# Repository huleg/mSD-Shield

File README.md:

# mSD-Shield
The mSD-Shield is a plug-on module with microSD socket, RTC (real time clock) with battery backup, prototyping area and optional 2.8" TFT-Display with Touch-Panel for Arduino.

## Shop
* [mSD-Shield v2](http://www.watterott.com/en/mSD-Shield-v2-Data-Logging-Shield)

## Features
* microSD socket (SPI) support SD and SDHC cards (up to 32GB)
* DS1307 RTC (I2C Real-Time-Clock) with backup battery
* Optional MI0283QT-Adapter (2.8" 320x240 Display with Touch-Panel)
* Prototyping Area

## Hardware
* 
* [Schematics + Layout](https://github.com/watterott/mSD-Shield/tree/master/hardware)
* **mSD-Shield v2.x**: For Uno, Leonardo and Mega with R3-Layout (SDA+SCL next to AREF)
* **mSD-Shield v1.x**: For Uno. On Mega/Leonardo boards only Software-SPI and no RTC without hardware modifications.
* **Mega mSD-Shield v1.x**: For Uno and Mega. Uno/Mega adjustment via jumper.

## Software
* [Arduino Library and Examples](https://github.com/watterott/Arduino-Libs)
* [Old Arduino Library and Examples](https://github.com/watterott/mSD-Shield/tree/5054db114faef1bcfd9c1d165ed713a681a0edea/src)

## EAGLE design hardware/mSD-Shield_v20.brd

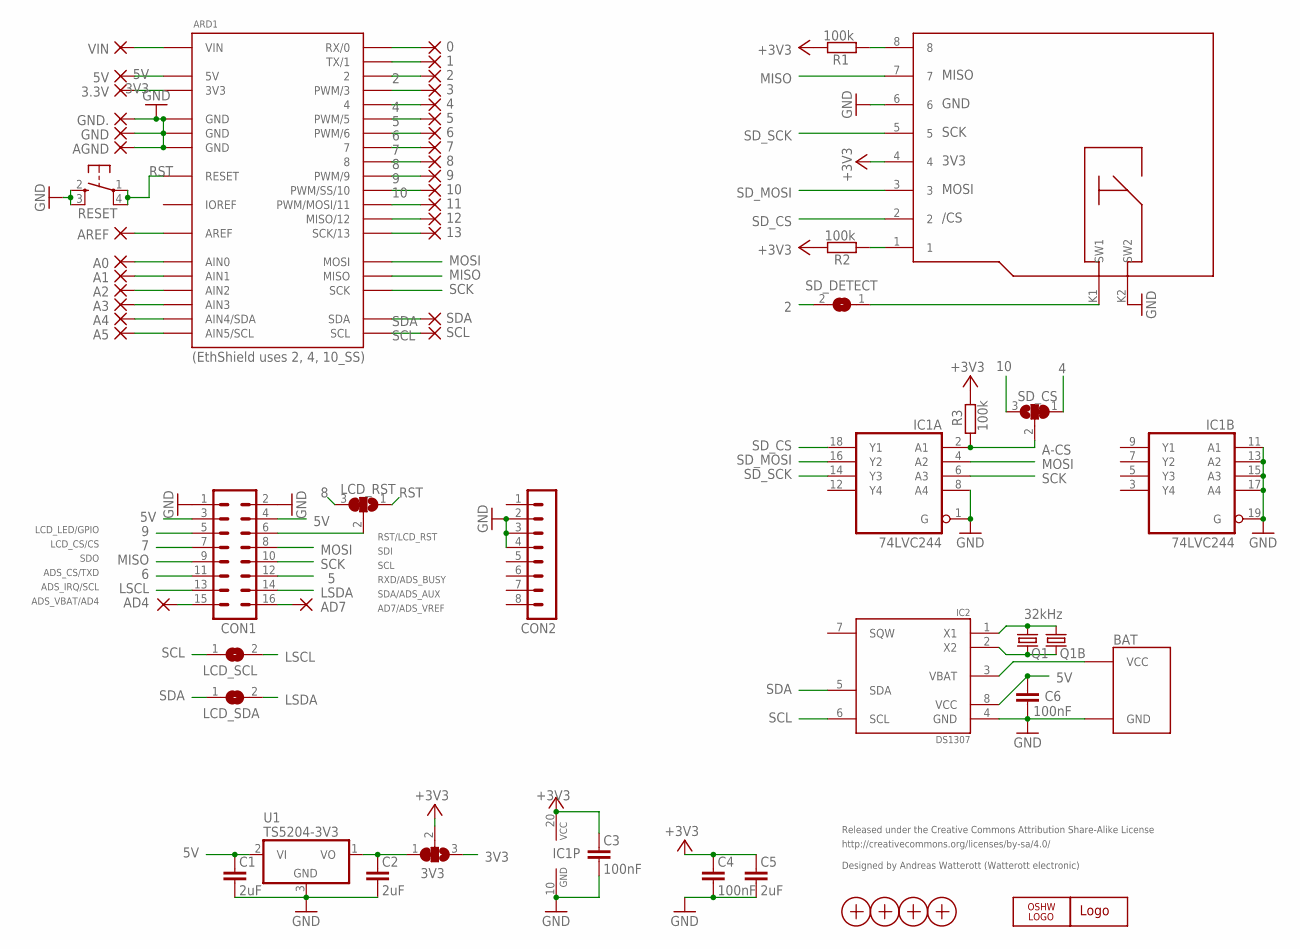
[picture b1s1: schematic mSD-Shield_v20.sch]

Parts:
0, 1, 2, 3, 3.3V, 4, 5, 5V, 6, 7, 8, 9, 10, 11, 12, 13: 1,6/0,8
3V3: SJ2W; SJ_2
A0, A1, A2, A3, A4, A5: 1,6/0,8
AD4, AD7: 1,6/0,8
AGND: 1,6/0,8
ARD1: UNO_ISP2
AREF: 1,6/0,8
BAT: 4UC-05581
C1, C2: 2uF; C0805
C3, C4, C6: 100nF; C0603
C5: 2uF; C0603
CON1: MA08-2
CON2: MA08-1
GND, GND.: 1,6/0,8
IC1: 74LVC244; SO20W
IC2: DS1307; SO8
LCD_RST: SJ2W; SJ_2
LCD_SCL: SJ
LCD_SDA: SJ
LOGO2: WE-LOGOPLACE; WE-LOGO
LOGO3: OSHW_LOGO_6MILX0100-NT; OSHW_6X100_NOTEXT
Q1: 32kHz; TC26V
Q1B: 32kHz; ZM315
R1, R2, R3: 100k; R0603
RESET: SW4S; SW_SMD4
SCL: 1,6/0,8
SDA: 1,6/0,8
SD_CS: SJ2W; SJ_2
SD_DETECT: SJ
U1: TS5204-3V3; SOT23
VIN: 1,6/0,8
X1, X2, X3, X4: PASSER
X5: MICRO-SD

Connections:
0: 0.1, ARD1.0 (RX/0)
1: 1.1, ARD1.1 (TX/1)
2: 2.1, ARD1.2, SD_DETECT.2
3: 3.1, ARD1.3 (PWM/3)
3V3: 3.3V.1, 3V3.3, ARD1.3V3
3V_OUT: 3V3.1, C2.1, U1.1 (VO)
4: 4.1, ARD1.4, SD_CS.1
5: 5.1, ARD1.5 (PWM/5), CON1.12
5V: 5V.1, ARD1.5V, C1.1, C6.2, CON1.3, CON1.4, IC2.8 (VCC), U1.2 (VI)
6: 6.1, ARD1.6 (PWM/6), CON1.11
7: 7.1, ARD1.7, CON1.7
8: 8.1, ARD1.8, LCD_RST.3
9: 9.1, ARD1.9 (PWM/9), CON1.5
10: 10.1, ARD1.10 (PWM/SS/10), SD_CS.3
11: 11.1, ARD1.11 (PWM/MOSI/11)
12: 12.1, ARD1.12 (MISO/12)
13: 13.1, ARD1.13 (SCK/13)
+3V3: 3V3.2, C3.1, C4.1, C5.1, IC1.20 (VCC), R1.1, R2.1, R3.2, X5.4
A-CS: IC1.2 (A1), R3.1, SD_CS.2
AD4: AD4.1, CON1.15
AD7: AD7.1, CON1.16
AIN0: A0.1, ARD1.AIN0
AIN1: A1.1, ARD1.AIN1
AIN2: A2.1, ARD1.AIN2
AIN3: A3.1, ARD1.AIN3
AIN4: A4.1, ARD1.AIN4 (AIN4/SDA)
AIN5: A5.1, ARD1.AIN5 (AIN5/SCL)
AREF: ARD1.AREF, AREF.1
GND: AGND.1, ARD1.GND@1 (GND), ARD1.GND@2 (GND), ARD1.GND@3 (GND), BAT.GND, C1.2, C2.2, C3.2, C4.2, C5.2, C6.1, CON1.1, CON1.2, CON2.2, CON2.3, CON2.4, GND.1, GND..1, IC1.1 (G), IC1.8 (A4), IC1.10 (GND), IC1.11 (A1), IC1.13 (A2), IC1.15 (A3), IC1.17 (A4), IC1.19 (G), IC2.4 (GND), RESET.2 (S), RESET.3 (S1), U1.3 (GND), X5.6, X5.K2 (SW2)
IOREF: ARD1.IOREF
LCD_RST: CON1.6, LCD_RST.2
LSCL: CON1.13, LCD_SCL.2
LSDA: CON1.14, LCD_SDA.2
MISO: ARD1.MISO, CON1.9, X5.7
MOSI: ARD1.MOSI, CON1.8, IC1.4 (A2)
unnamed: R2.2, X5.1
unnamed: R1.2, X5.8
RST: ARD1.RST (RESET), LCD_RST.1, RESET.1, RESET.4 (P1)
SCK: ARD1.SCK, CON1.10, IC1.6 (A3)
SCL: ARD1.SCL, IC2.6 (SCL), LCD_SCL.1, SCL.1
SDA: ARD1.SDA, IC2.5 (SDA), LCD_SDA.1, SDA.1
SD_CS: IC1.18 (Y1), X5.2
SD_DET: SD_DETECT.1, X5.K1 (SW1)
SD_MOSI: IC1.16 (Y2), X5.3
SD_SCK: IC1.14 (Y3), X5.5
VBAT: BAT.VCC, IC2.3 (VBAT)
VIN: ARD1.VIN, VIN.1
X1: IC2.1 (X1), Q1.2, Q1B.2
X2: IC2.2 (X2), Q1.1, Q1B.1

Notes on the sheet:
Released under the Creative Commons Attribution Share-Alike License
http://creativecommons.org/licenses/by-sa/4.0/
Designed by Andreas Watterott (Watterott electronic)
(EthShield uses 2, 4, 10_SS)
LCD_LED/GPIO
LCD_CS/CS
SDO
ADS_CS/TXD
ADS_IRQ/SCL
ADS_VBAT/AD4
AD7/ADS_VREF
SDA/ADS_AUX
RXD/ADS_BUSY
SCL
SDI
RST/LCD_RST

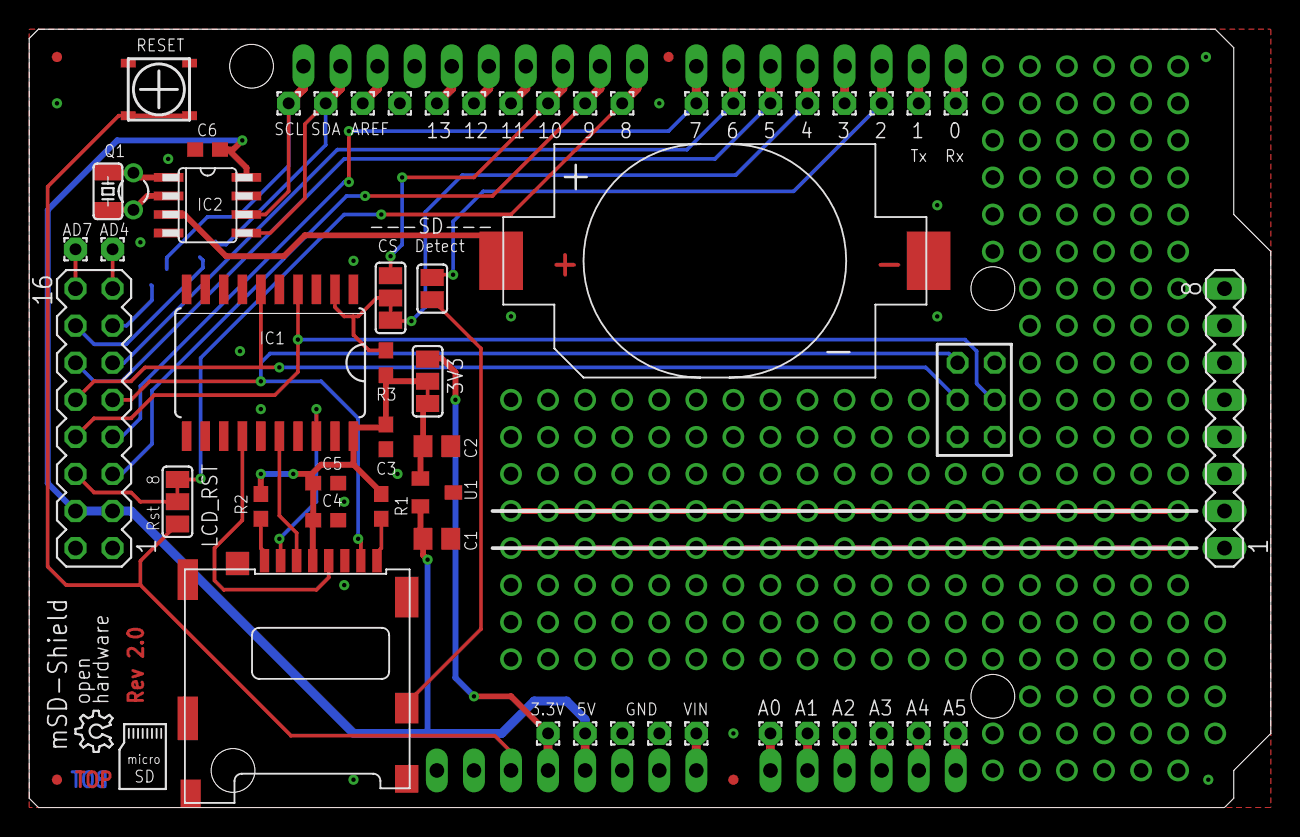
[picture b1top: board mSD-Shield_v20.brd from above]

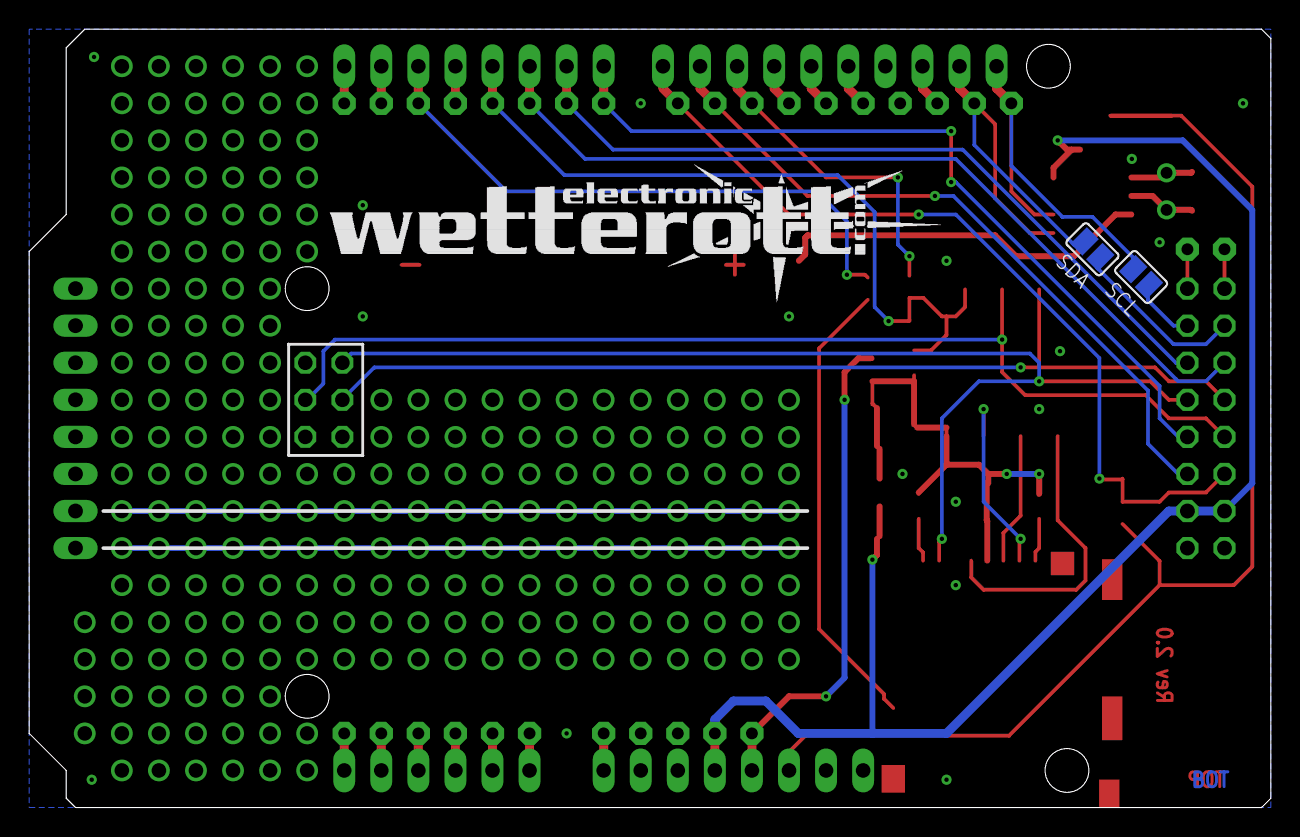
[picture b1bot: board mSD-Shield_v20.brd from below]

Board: 2 copper layers, 85.1 x 53.3 mm, 63 parts (3 on the bottom side), 48 nets.

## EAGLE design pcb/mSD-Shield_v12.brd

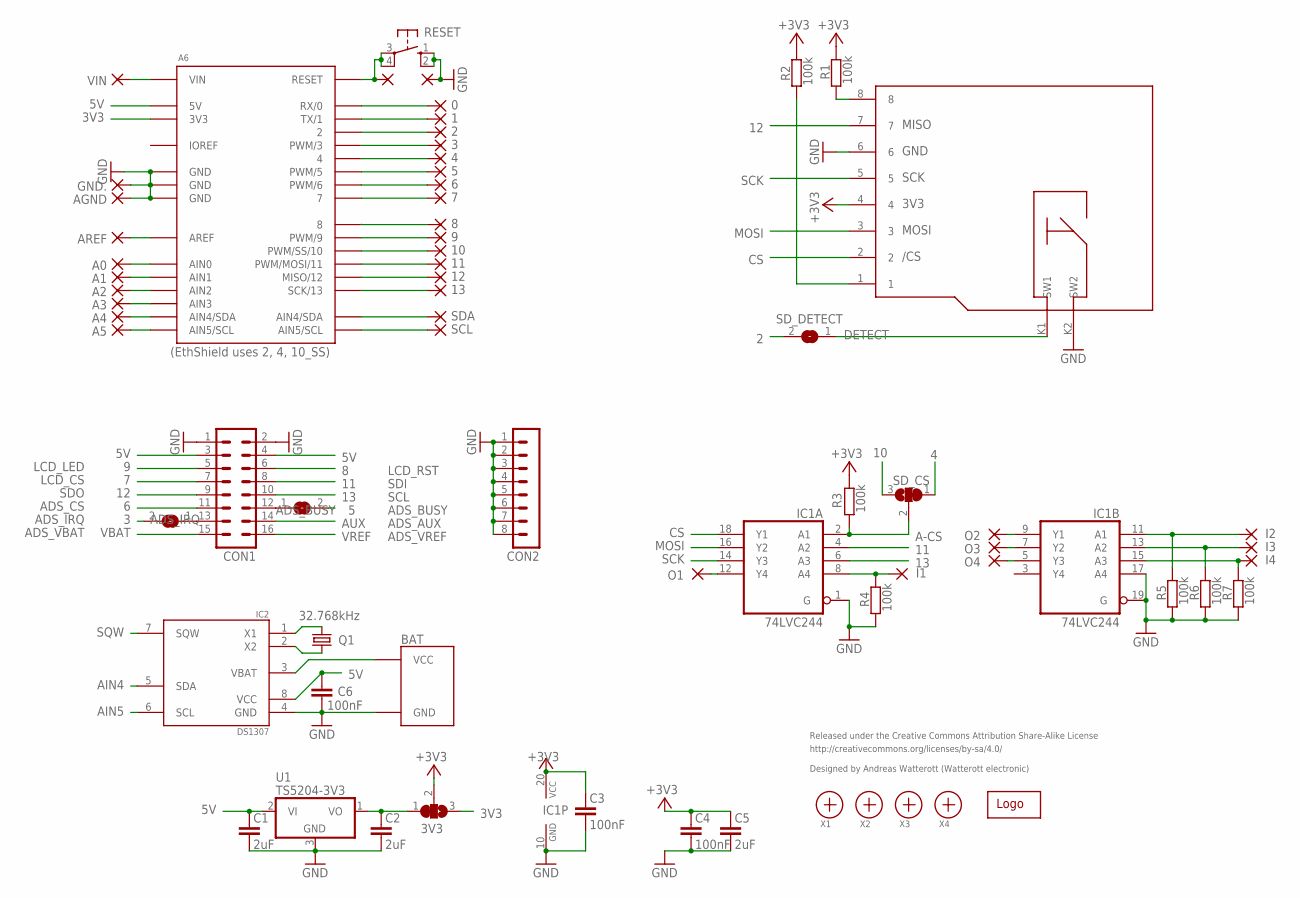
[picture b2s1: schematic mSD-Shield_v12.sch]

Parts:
0, 1, 2, 3, 4, 5, 6, 7, 8, 9, 10, 11, 12, 13: 1,6/0,8
3V3: SJ2W; SJ_2
A0, A1, A2, A3, A4, A5: 1,6/0,8
A6: UNO2
ADS_BUSY: SJ
ADS_IRQ: SJ
AGND: 1,6/0,8
AREF: 1,6/0,8
BAT: 4UC-05581
C1, C2: 2uF; C0805
C3, C4, C6: 100nF; C0603
C5: 2uF; C0603
CON1: MA08-2
CON2: MA08-1
GND: SMD2; SMD1,27-2,54
GND.: 1,6/0,8
I1, I2, I3, I4: SMD2; SMD1,27-2,54
IC1: 74LVC244; SO20W
IC2: DS1307; SO8
O1, O2, O3, O4: SMD2; SMD1,27-2,54
Q1: 32.768kHz; TC26V
R1, R2, R3, R4, R5, R6, R7: 100k; R0603
RESET: 10-XX; B3F-10XX
RST: SMD2; SMD1,27-2,54
SCL: 1,6/0,8
SDA: 1,6/0,8
SD_CS: SJ2W; SJ_2
SD_DETECT: SJ
U1: TS5204-3V3; SOT23
U$1: WE-LOGO
VIN: 1,6/0,8
X1, X2, X3, X4: PASSER
X5: MICRO-SD

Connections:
0: 0.1, A6.0 (RX/0)
1: 1.1, A6.1 (TX/1)
2: 2.1, A6.2, SD_DETECT.2
3: 3.1, A6.3 (PWM/3), ADS_IRQ.2
3V3: 3V3.3, A6.3V3
3V_OUT: 3V3.1, C2.1, U1.1 (VO)
4: 4.1, A6.4, SD_CS.1
5: 5.1, A6.5 (PWM/5), ADS_BUSY.2
5V: A6.5V, C1.1, C6.2, CON1.3, CON1.4, IC2.8 (VCC), U1.2 (VI)
6: 6.1, A6.6 (PWM/6), CON1.11
7: 7.1, A6.7, CON1.7
8: 8.1, A6.8, CON1.6
9: 9.1, A6.9 (PWM/9), CON1.5
10: 10.1, A6.10 (PWM/SS/10), SD_CS.3
11: 11.1, A6.11 (PWM/MOSI/11), CON1.8, IC1.4 (A2)
12: 12.1, A6.12 (MISO/12), CON1.9, X5.7
13: 13.1, A6.13 (SCK/13), CON1.10, IC1.6 (A3)
+3V3: 3V3.2, C3.1, C4.1, C5.1, IC1.20 (VCC), R1.1, R2.1, R3.2, X5.4
A-CS: IC1.2 (A1), R3.1, SD_CS.2
ADS_BUSY: ADS_BUSY.1, CON1.12
ADS_IRQ: ADS_IRQ.1, CON1.13
AIN0: A0.1, A6.AIN0
AIN1: A1.1, A6.AIN1
AIN2: A2.1, A6.AIN2
AIN3: A3.1, A6.AIN3
AIN4: A4.1, A6.AIN4 (AIN4/SDA), IC2.5 (SDA)
AIN5: A5.1, A6.AIN5 (AIN5/SCL), IC2.6 (SCL)
AUX: CON1.14
BAT: BAT.VCC, IC2.3 (VBAT)
CS: IC1.18 (Y1), X5.2
DETECT: SD_DETECT.1, X5.K1 (SW1)
GND: A6.GND@1 (GND), A6.GND@2 (GND), A6.GND@3 (GND), AGND.1, BAT.GND, C1.2, C2.2, C3.2, C4.2, C5.2, C6.1, CON1.1, CON1.2, CON2.1, CON2.2, CON2.3, CON2.4, CON2.5, CON2.6, CON2.7, CON2.8, GND.1, GND..1, IC1.1 (G), IC1.10 (GND), IC1.17 (A4), IC1.19 (G), IC2.4 (GND), R4.1, R5.1, R6.1, R7.1, RESET.1 (S), RESET.2 (S1), U1.3 (GND), X5.6, X5.K2 (SW2)
I-1: I1.1, IC1.8 (A4), R4.2
I-2: I2.1, IC1.11 (A1), R5.2
I-3: I3.1, IC1.13 (A2), R6.2
I-4: I4.1, IC1.15 (A3), R7.2
IOREF: A6.IOREF
MOSI: IC1.16 (Y2), X5.3
unnamed: R2.2, X5.1
unnamed: R1.2, X5.8
unnamed: A6.VIN, VIN.1
unnamed: A6.SDA (AIN4/SDA), SDA.1
unnamed: A6.SCL (AIN5/SCL), SCL.1
unnamed: IC2.1 (X1), Q1.2
unnamed: IC2.2 (X2), Q1.1
unnamed: A6.AREF, AREF.1
O-1: IC1.12 (Y4), O1.1
O-2: IC1.9 (Y1), O2.1
O-3: IC1.7 (Y2), O3.1
O-4: IC1.5 (Y3), O4.1
RST: A6.RST (RESET), RESET.3, RESET.4 (P1), RST.1
SCK: IC1.14 (Y3), X5.5
SQW: IC2.7 (SQW)
VBAT: CON1.15
VREF: CON1.16

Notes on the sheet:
Released under the Creative Commons Attribution Share-Alike License
http://creativecommons.org/licenses/by-sa/4.0/
Designed by Andreas Watterott (Watterott electronic)
(EthShield uses 2, 4, 10_SS)
LCD_LED
LCD_CS
SDO
ADS_CS
ADS_IRQ
ADS_VBAT
ADS_VREF
ADS_AUX
ADS_BUSY
SCL
SDI
LCD_RST

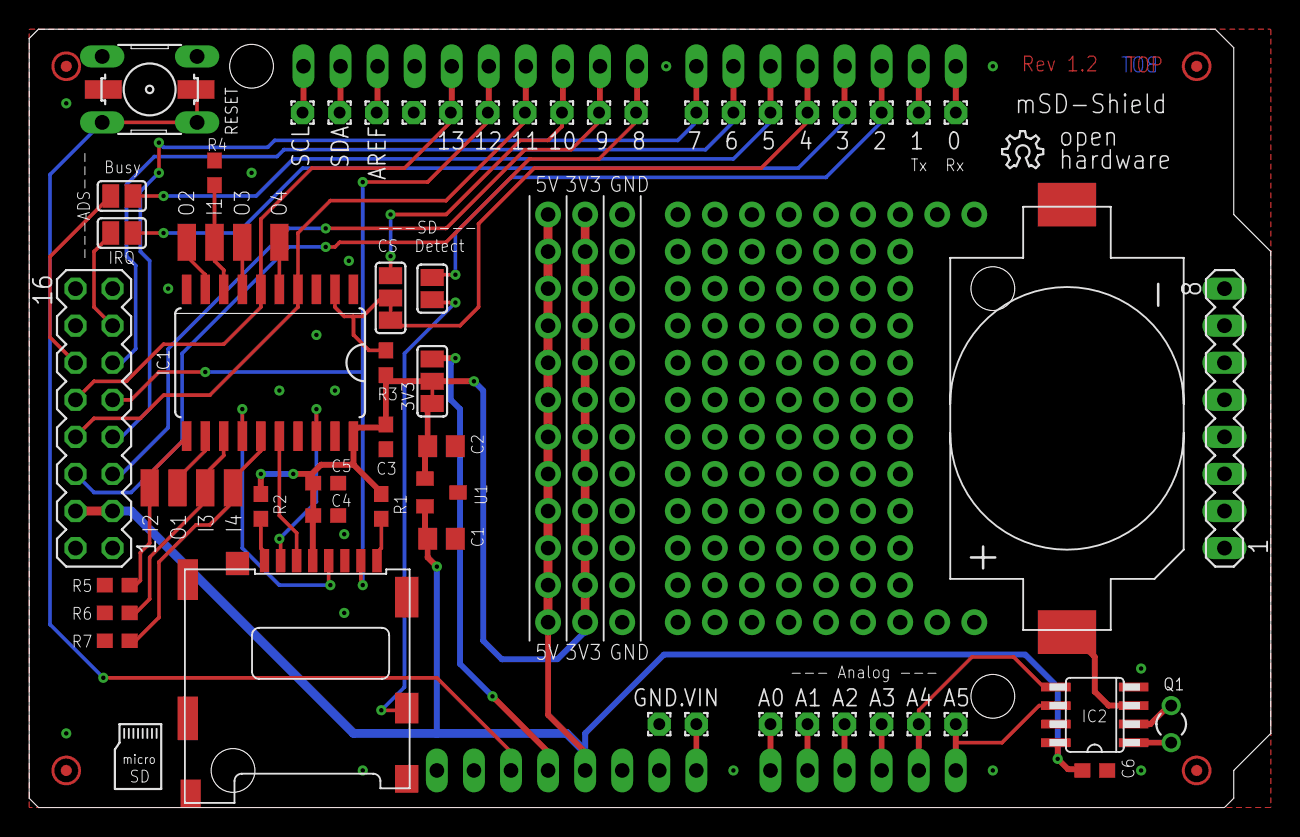
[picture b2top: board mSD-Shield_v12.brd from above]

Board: 2 copper layers, 85.1 x 53.3 mm, 70 parts (1 on the bottom side), 50 nets.

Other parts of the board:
LOGO1: OSHW_LOGO_6MILX0100-NT; OSHW_6X100_NOTEXT

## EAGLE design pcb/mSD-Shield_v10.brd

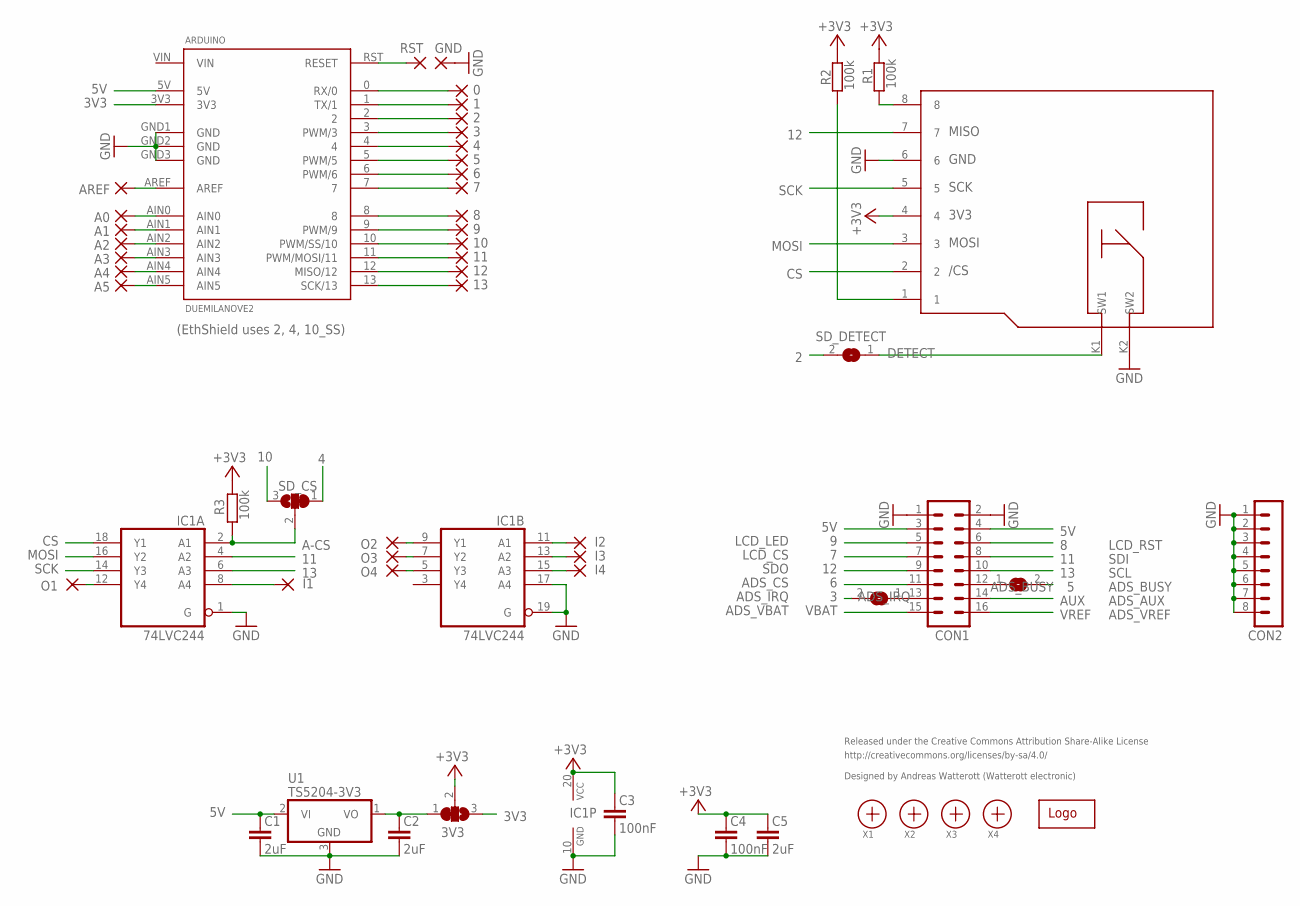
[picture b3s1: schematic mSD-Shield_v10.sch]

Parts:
0, 1, 2, 3, 4, 5, 6, 7, 8, 9, 10, 11, 12, 13: 1,6/0,8
3V3: SJ2W; SJ_2
A0, A1, A2, A3, A4, A5: 1,6/0,8
ADS_BUSY: SJ
ADS_IRQ: SJ
ARDUINO: DUEMILANOVE2
AREF: 1,6/0,8
C1, C2: 2uF; C0805
C3, C4: 100nF; C0603
C5: 2uF; C0603
CON1: MA08-2
CON2: MA08-1
GND: SMD2; SMD1,27-2,54
I1, I2, I3, I4: SMD2; SMD1,27-2,54
IC1: 74LVC244; SO20W
O1, O2, O3, O4: SMD2; SMD1,27-2,54
R1, R2, R3: 100k; R0603
RST: SMD2; SMD1,27-2,54
SD_CS: SJ2W; SJ_2
SD_DETECT: SJ
U1: TS5204-3V3; SOT23
U$1: WE-LOGO
X1, X2, X3, X4: PASSER
X5: MICRO-SD

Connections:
0: 0.1, ARDUINO.0 (RX/0)
1: 1.1, ARDUINO.1 (TX/1)
2: 2.1, ARDUINO.2, SD_DETECT.2
3: 3.1, ADS_IRQ.2, ARDUINO.3 (PWM/3)
3V3: 3V3.3, ARDUINO.3V3
3V_OUT: 3V3.1, C2.1, U1.1 (VO)
4: 4.1, ARDUINO.4, SD_CS.1
5: 5.1, ADS_BUSY.2, ARDUINO.5 (PWM/5)
5V: ARDUINO.5V, C1.1, CON1.3, CON1.4, U1.2 (VI)
6: 6.1, ARDUINO.6 (PWM/6), CON1.11
7: 7.1, ARDUINO.7, CON1.7
8: 8.1, ARDUINO.8, CON1.6
9: 9.1, ARDUINO.9 (PWM/9), CON1.5
10: 10.1, ARDUINO.10 (PWM/SS/10), SD_CS.3
11: 11.1, ARDUINO.11 (PWM/MOSI/11), CON1.8, IC1.4 (A2)
12: 12.1, ARDUINO.12 (MISO/12), CON1.9, X5.7
13: 13.1, ARDUINO.13 (SCK/13), CON1.10, IC1.6 (A3)
+3V3: 3V3.2, C3.1, C4.1, C5.1, IC1.20 (VCC), R1.1, R2.1, R3.2, X5.4
A-CS: IC1.2 (A1), R3.1, SD_CS.2
ADS_BUSY: ADS_BUSY.1, CON1.12
ADS_IRQ: ADS_IRQ.1, CON1.13
AIN0: A0.1, ARDUINO.AIN0
AIN1: A1.1, ARDUINO.AIN1
AIN2: A2.1, ARDUINO.AIN2
AIN3: A3.1, ARDUINO.AIN3
AIN4: A4.1, ARDUINO.AIN4
AIN5: A5.1, ARDUINO.AIN5
AUX: CON1.14
CS: IC1.18 (Y1), X5.2
DETECT: SD_DETECT.1, X5.K1 (SW1)
GND: ARDUINO.GND1 (GND), ARDUINO.GND2 (GND), ARDUINO.GND3 (GND), C1.2, C2.2, C3.2, C4.2, C5.2, CON1.1, CON1.2, CON2.1, CON2.2, CON2.3, CON2.4, CON2.5, CON2.6, CON2.7, CON2.8, GND.1, IC1.1 (G), IC1.10 (GND), IC1.17 (A4), IC1.19 (G), U1.3 (GND), X5.6, X5.K2 (SW2)
I-1: I1.1, IC1.8 (A4)
I-2: I2.1, IC1.11 (A1)
I-3: I3.1, IC1.13 (A2)
I-4: I4.1, IC1.15 (A3)
MOSI: IC1.16 (Y2), X5.3
unnamed: R2.2, X5.1
unnamed: R1.2, X5.8
unnamed: ARDUINO.AREF, AREF.1
O-1: IC1.12 (Y4), O1.1
O-2: IC1.9 (Y1), O2.1
O-3: IC1.7 (Y2), O3.1
O-4: IC1.5 (Y3), O4.1
RST: ARDUINO.RST (RESET), RST.1
SCK: IC1.14 (Y3), X5.5
VBAT: CON1.15
VIN: ARDUINO.VIN
VREF: CON1.16

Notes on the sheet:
Released under the Creative Commons Attribution Share-Alike License
http://creativecommons.org/licenses/by-sa/4.0/
Designed by Andreas Watterott (Watterott electronic)
(EthShield uses 2, 4, 10_SS)
LCD_LED
LCD_CS
SDO
ADS_CS
ADS_IRQ
ADS_VBAT
ADS_VREF
ADS_AUX
ADS_BUSY
SCL
SDI
LCD_RST

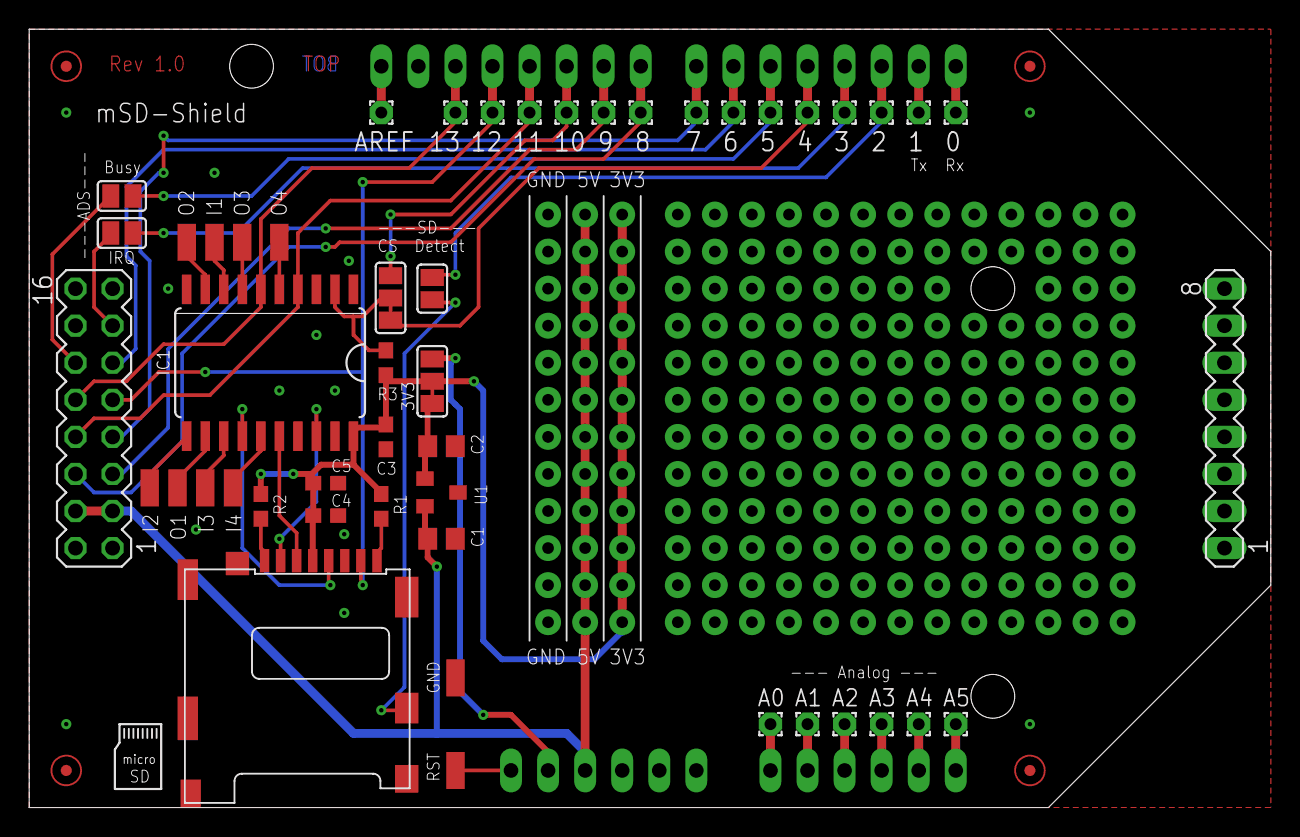
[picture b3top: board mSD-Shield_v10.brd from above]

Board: 2 copper layers, 85.1 x 53.3 mm, 55 parts (1 on the bottom side), 44 nets.

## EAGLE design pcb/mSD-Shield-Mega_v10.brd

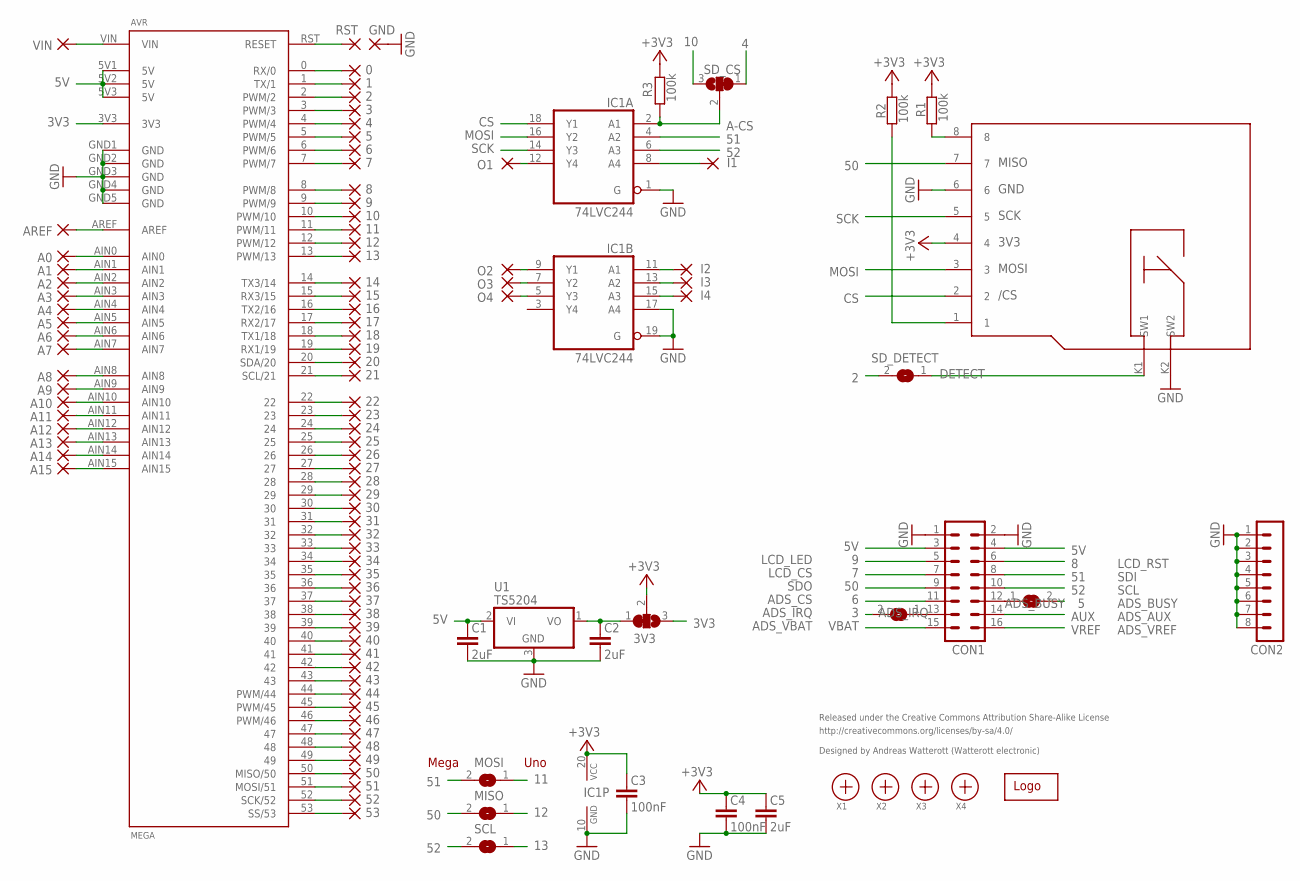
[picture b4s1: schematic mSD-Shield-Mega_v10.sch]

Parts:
0, 1, 2, 3, 4, 5, 6, 7, 8, 9, 10, 11, 12, 13, 14, 15, 16, 17, 18, 19, 20, 21, 22, 23, 24, 25, 26, 27, 28, 29, 30, 31, 32, 33, 34, 35, 36, 37, 38, 39, 40, 41, 42, 43, 44, 45, 46, 47, 48, 49, 50, 51, 52, 53: 1,6/0,8
3V3: SJ2W; SJ_2
A0, A1, A2, A3, A4, A5, A6, A7, A8, A9, A10, A11, A12, A13, A14, A15: 1,6/0,8
ADS_BUSY: SJ
ADS_IRQ: SJ
AREF: 1,6/0,8
AVR: MEGA
C1, C2: 2uF; C0805
C3, C4: 100nF; C0603
C5: 2uF; C0603
CON1: MA08-2
CON2: MA08-1
GND: SMD2; SMD1,27-2,54
I1, I2, I3, I4: SMD2; SMD1,27-2,54
IC1: 74LVC244; SO20W
MISO: SJ
MOSI: SJ
O1, O2, O3, O4: SMD2; SMD1,27-2,54
R1, R2, R3: 100k; R0603
RST: SMD2; SMD1,27-2,54
SCL: SJ
SD_CS: SJ2W; SJ_2
SD_DETECT: SJ
U1: TS5204; SOT23
U$1: WE-LOGO
VIN: 1,6/0,8
X1, X2, X3, X4: PASSER
X5: MICRO-SD

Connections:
0: 0.1, AVR.0 (RX/0)
1: 1.1, AVR.1 (TX/1)
2: 2.1, AVR.2 (PWM/2), SD_DETECT.2
3: 3.1, ADS_IRQ.2, AVR.3 (PWM/3)
3V3: 3V3.3, AVR.3V3
3V_OUT: 3V3.1, C2.1, U1.1 (VO)
4: 4.1, AVR.4 (PWM/4), SD_CS.1
5: 5.1, ADS_BUSY.2, AVR.5 (PWM/5)
5V: AVR.5V1 (5V), AVR.5V2 (5V), AVR.5V3 (5V), C1.1, CON1.3, CON1.4, U1.2 (VI)
6: 6.1, AVR.6 (PWM/6), CON1.11
7: 7.1, AVR.7 (PWM/7), CON1.7
8: 8.1, AVR.8 (PWM/8), CON1.6
9: 9.1, AVR.9 (PWM/9), CON1.5
10: 10.1, AVR.10 (PWM/10), SD_CS.3
11: 11.1, AVR.11 (PWM/11), MOSI.1
12: 12.1, AVR.12 (PWM/12), MISO.1
13: 13.1, AVR.13 (PWM/13), SCL.1
14: 14.1, AVR.14 (TX3/14)
15: 15.1, AVR.15 (RX3/15)
16: 16.1, AVR.16 (TX2/16)
17: 17.1, AVR.17 (RX2/17)
18: 18.1, AVR.18 (TX1/18)
19: 19.1, AVR.19 (RX1/19)
20: 20.1, AVR.20 (SDA/20)
21: 21.1, AVR.21 (SCL/21)
22: 22.1, AVR.22
23: 23.1, AVR.23
24: 24.1, AVR.24
25: 25.1, AVR.25
26: 26.1, AVR.26
27: 27.1, AVR.27
28: 28.1, AVR.28
29: 29.1, AVR.29
30: 30.1, AVR.30
31: 31.1, AVR.31
32: 32.1, AVR.32
33: 33.1, AVR.33
34: 34.1, AVR.34
35: 35.1, AVR.35
36: 36.1, AVR.36
37: 37.1, AVR.37
38: 38.1, AVR.38
39: 39.1, AVR.39
40: 40.1, AVR.40
41: 41.1, AVR.41
42: 42.1, AVR.42
43: 43.1, AVR.43
44: 44.1, AVR.44 (PWM/44)
45: 45.1, AVR.45 (PWM/45)
46: 46.1, AVR.46 (PWM/46)
47: 47.1, AVR.47
48: 48.1, AVR.48
49: 49.1, AVR.49
50: 50.1, AVR.50 (MISO/50), CON1.9, MISO.2, X5.7
51: 51.1, AVR.51 (MOSI/51), CON1.8, IC1.4 (A2), MOSI.2
52: 52.1, AVR.52 (SCK/52), CON1.10, IC1.6 (A3), SCL.2
53: 53.1, AVR.53 (SS/53)
+3V3: 3V3.2, C3.1, C4.1, C5.1, IC1.20 (VCC), R1.1, R2.1, R3.2, X5.4
A-CS: IC1.2 (A1), R3.1, SD_CS.2
ADS_BUSY: ADS_BUSY.1, CON1.12
ADS_IRQ: ADS_IRQ.1, CON1.13
AIN0: A0.1, AVR.AIN0
AIN1: A1.1, AVR.AIN1
AIN2: A2.1, AVR.AIN2
AIN3: A3.1, AVR.AIN3
AIN4: A4.1, AVR.AIN4
AIN5: A5.1, AVR.AIN5
AIN6: A6.1, AVR.AIN6
AIN7: A7.1, AVR.AIN7
AIN8: A8.1, AVR.AIN8
AIN9: A9.1, AVR.AIN9
AIN10: A10.1, AVR.AIN10
AIN11: A11.1, AVR.AIN11
AIN12: A12.1, AVR.AIN12
AIN13: A13.1, AVR.AIN13
AIN14: A14.1, AVR.AIN14
AIN15: A15.1, AVR.AIN15
AUX: CON1.14
CS: IC1.18 (Y1), X5.2
DETECT: SD_DETECT.1, X5.K1 (SW1)
GND: AVR.GND1 (GND), AVR.GND2 (GND), AVR.GND3 (GND), AVR.GND4 (GND), AVR.GND5 (GND), C1.2, C2.2, C3.2, C4.2, C5.2, CON1.1, CON1.2, CON2.1, CON2.2, CON2.3, CON2.4, CON2.5, CON2.6, CON2.7, CON2.8, GND.1, IC1.1 (G), IC1.10 (GND), IC1.17 (A4), IC1.19 (G), U1.3 (GND), X5.6, X5.K2 (SW2)
I-1: I1.1, IC1.8 (A4)
I-2: I2.1, IC1.11 (A1)
I-3: I3.1, IC1.13 (A2)
I-4: I4.1, IC1.15 (A3)
MOSI: IC1.16 (Y2), X5.3
unnamed: R2.2, X5.1
unnamed: R1.2, X5.8
unnamed: AVR.VIN, VIN.1
unnamed: AREF.1, AVR.AREF
O-1: IC1.12 (Y4), O1.1
O-2: IC1.9 (Y1), O2.1
O-3: IC1.7 (Y2), O3.1
O-4: IC1.5 (Y3), O4.1
RST: AVR.RST (RESET), RST.1
SCK: IC1.14 (Y3), X5.5
VBAT: CON1.15
VREF: CON1.16

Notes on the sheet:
Released under the Creative Commons Attribution Share-Alike License
http://creativecommons.org/licenses/by-sa/4.0/
Designed by Andreas Watterott (Watterott electronic)
LCD_LED
LCD_CS
SDO
ADS_CS
ADS_IRQ
ADS_VBAT
ADS_VREF
ADS_AUX
ADS_BUSY
SCL
SDI
LCD_RST
Uno
Mega

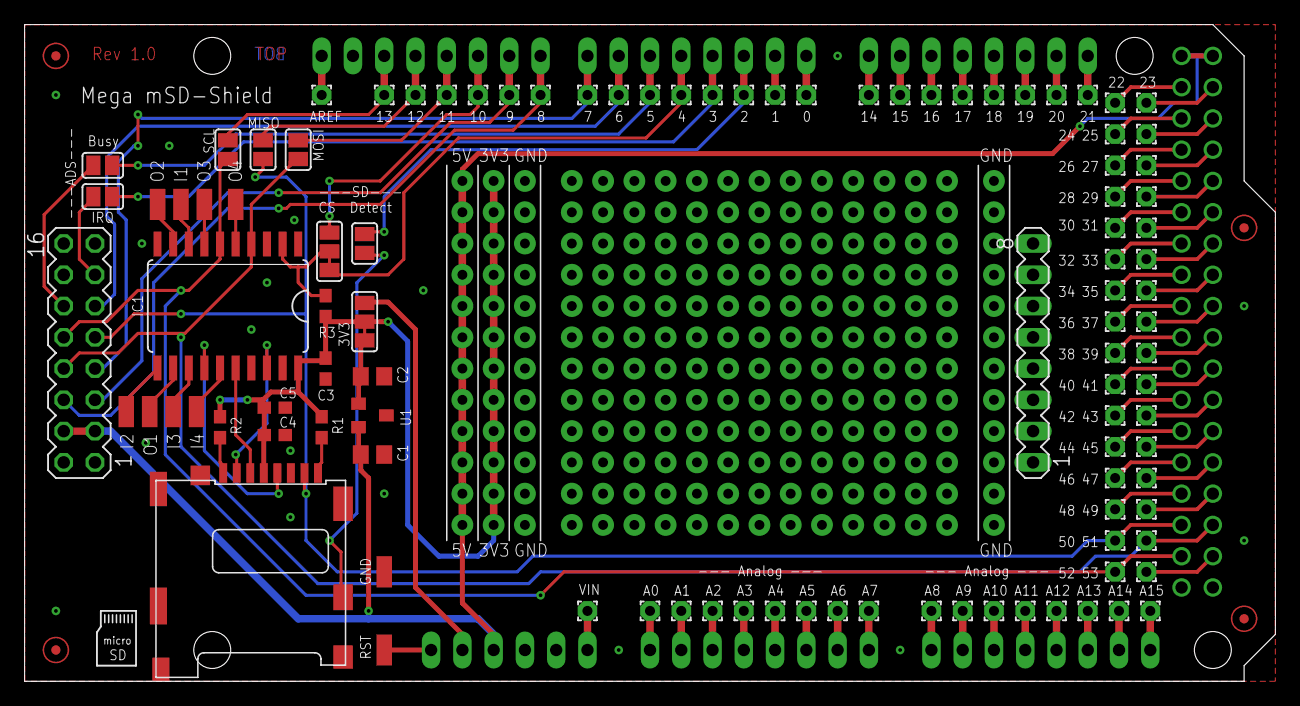
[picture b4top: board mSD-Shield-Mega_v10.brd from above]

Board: 2 copper layers, 101.6 x 53.3 mm, 109 parts (1 on the bottom side), 95 nets.

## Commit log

2012-07-31 examples updated
2012-12-14 added new pcb rev
2013-01-30 added support for MI0283QT9 improved ADS7846 lib
2013-05-20 added Leonardo support
2013-05-27 updated docu
2013-08-08 added v2 pcb
2013-10-01 updated image
2013-10-01 Lib v0.21
2013-10-09 updated readme and docu
2013-10-22 updated schematics
2014-01-03 updated libraries
2014-01-06 moved examples to Arduino-Libs repository
2014-03-10 updated license infos
2014-08-15 updated schematic and layout files
2014-08-21 updated layout and schematics
2014-11-06 cleaned up schematics and layout
2015-01-11 moved image
2015-08-21 changed path structure
